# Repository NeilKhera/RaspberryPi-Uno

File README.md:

## RaspberryPi-Uno
<br/>

### Description
A pin-compatible Arduino Uno clone board for the Raspberry Pi RP2040 microcontroller.

Check out the resources folder for Circuitpython config files, or the Releases section for the compiled firmware .uf2!

### License

Designed by Neil Khera.

Creative Commons Attribution/Share-Alike, all text above must be included in any redistribution. See license.txt for additional details.

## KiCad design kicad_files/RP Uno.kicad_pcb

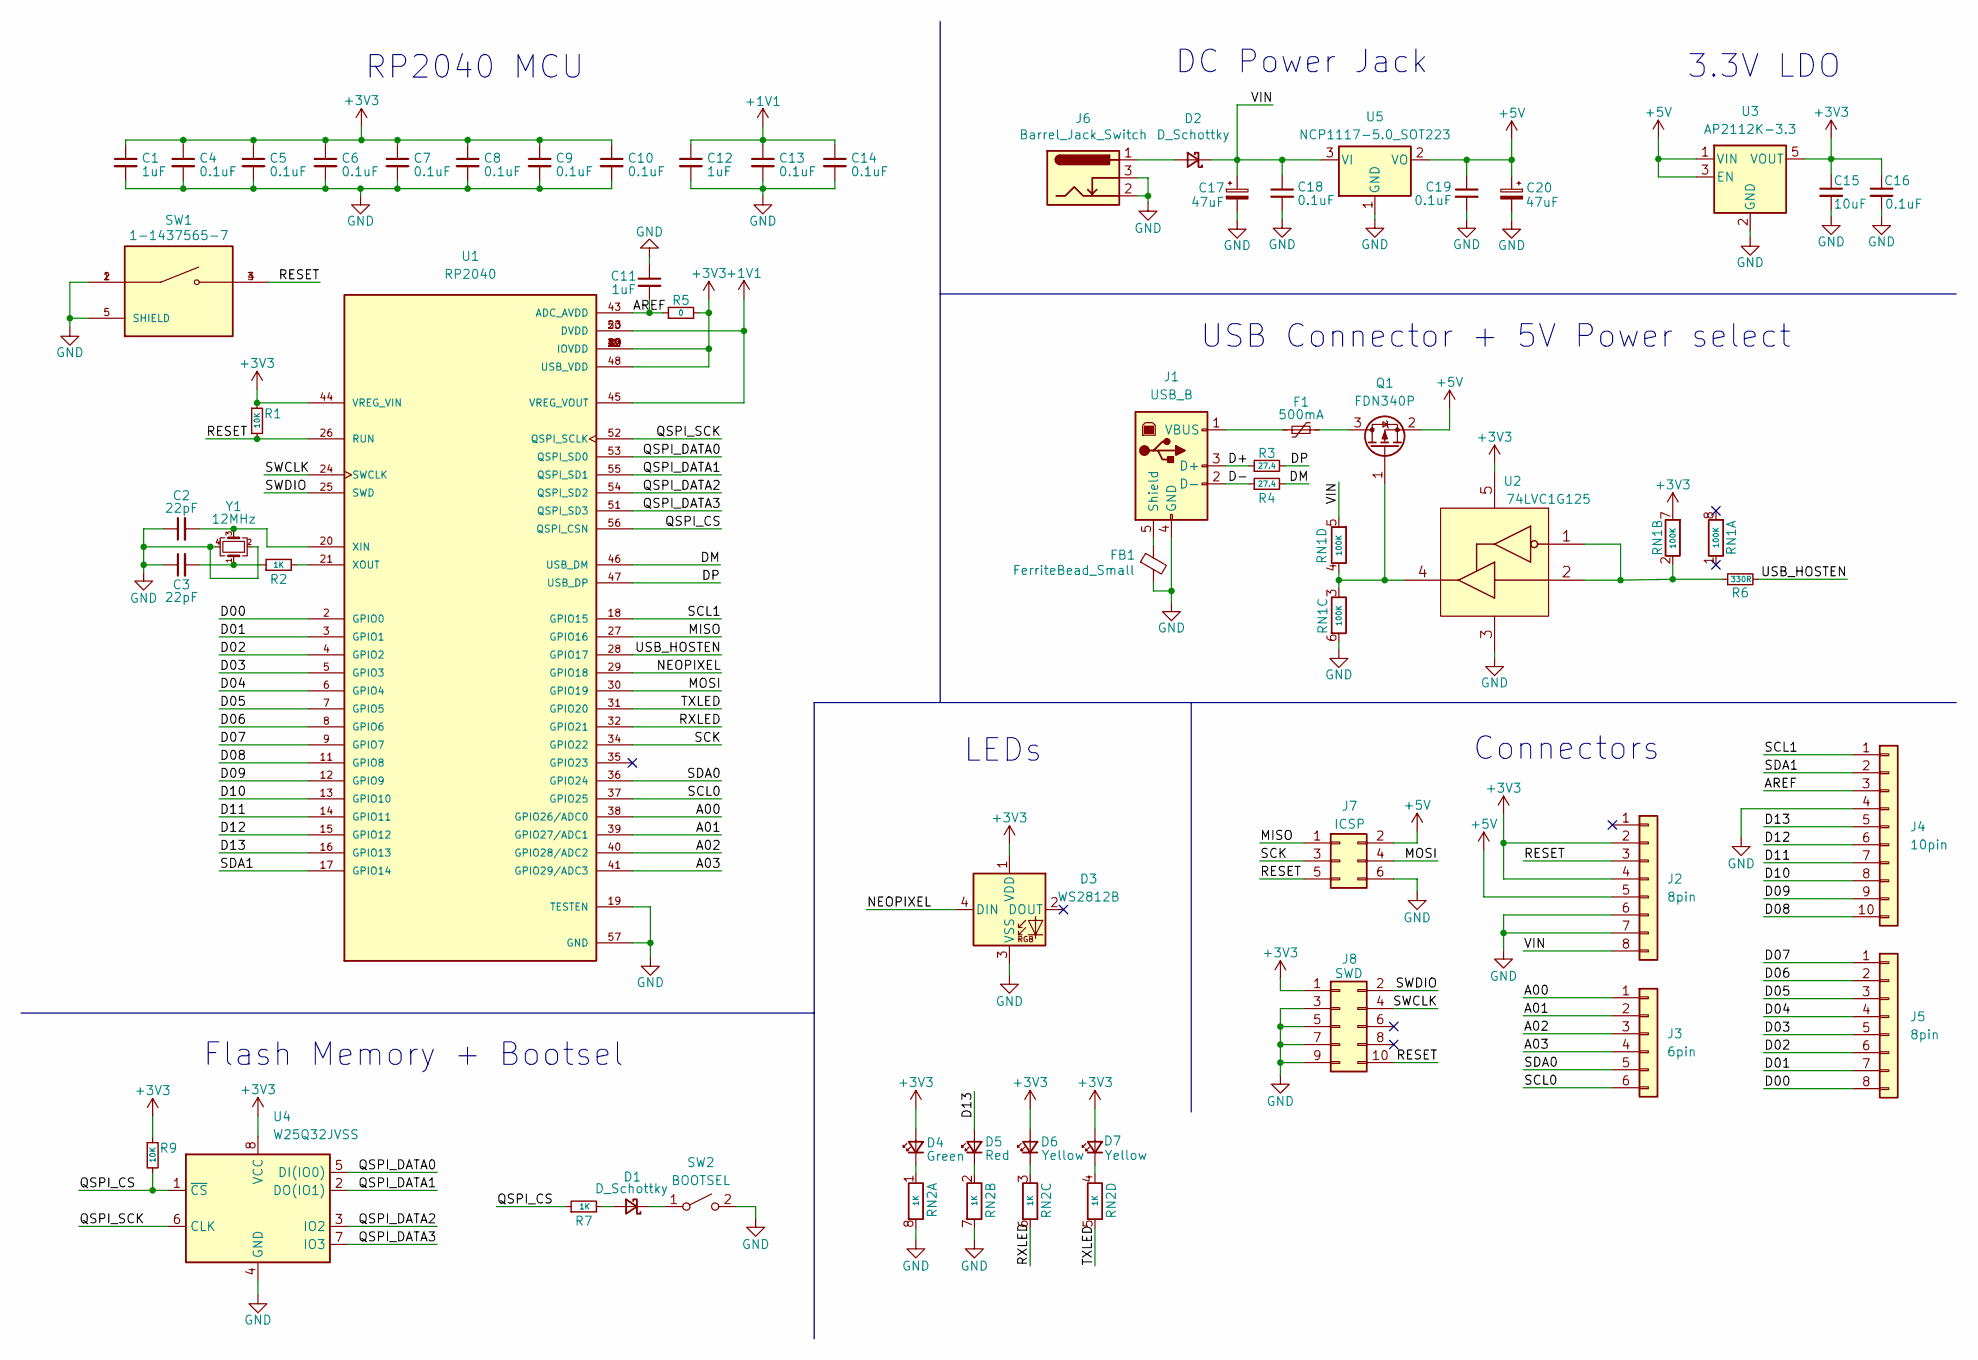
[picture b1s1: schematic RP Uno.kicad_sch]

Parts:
C1, C11, C12: 1uF; C_0603_1608Metric
C2, C3: 22pF; C_0603_1608Metric
C4, C5, C6, C7, C8, C9, C10, C13, C14, C16, C18, C19: 0.1uF; C_0603_1608Metric
C15: 10uF; C_0603_1608Metric
C17, C20: 47uF; CAPAE680X600N
D1: D_Schottky; D_SOD-323
D2: D_Schottky; D_SMB
D3: WS2812B; LED_WS2812B_PLCC4_5.0x5.0mm_P3.2mm
D4: Green; LED_0603_1608Metric
D5: Red; LED_0603_1608Metric
D6, D7: Yellow; LED_0603_1608Metric
F1: 500mA; Fuse_1206_3216Metric
FB1: FerriteBead_Small; L_0603_1608Metric
J1: USB_B; USB_B_OST_USB-B1HSxx_Horizontal
J2, J5: 8pin; PinSocket_1x08_P2.54mm_Vertical
J3: 6pin; PinSocket_1x06_P2.54mm_Vertical
J4: 10pin; PinSocket_1x10_P2.54mm_Vertical
J6: Barrel_Jack_Switch; BarrelJack_Horizontal
J7: ICSP; PinHeader_2x03_P2.54mm_Vertical
J8: SWD; 2X05_1.27MM_BOX_POSTS
Q1: FDN340P; SOT-23
R1, R9: 10K; R_0603_1608Metric
R2, R7: 1K; R_0603_1608Metric
R3, R4: 27.4; R_0603_1608Metric
R5: 0; R_0603_1608Metric
R6: 330R; R_0603_1608Metric
RN1: 100K; R_Array_Concave_4x0603
RN2: 1K; R_Array_Concave_4x0603
SW1: 1-1437565-7; SW_1-1437565-7
SW2: BOOTSEL; SW_SPST_B3U-1000P
U1: RP2040; QFN40P700X700X90-57N; PARTREV 1.6.1
U2: 74LVC1G125; SOT-23-5
U3: AP2112K-3.3; SOT-23-5
U4: W25Q32JVSS; SOIC-8_5.23x5.23mm_P1.27mm
U5: NCP1117-5.0_SOT223; SOT-223-3_TabPin2
Y1: 12MHz; Crystal_SMD_2520-4Pin_2.5x2.0mm

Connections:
+1V1: C12.1, C13.1, C14.1, U1.23 (DVDD), U1.45 (VREG_VOUT), U1.50 (DVDD)
+3V3: C1.1, C4.1, C5.1, C6.1, C7.1, C8.1, C9.1, C10.1, C15.1, C16.1, D3.1 (VDD), D4.2 (A), D6.2 (A), D7.2 (A), J2.2, J2.4, J8.1, R1.1, R5.2, R9.1, RN1.7 (R2.2), U1.1 (IOVDD), U1.10 (IOVDD), U1.22 (IOVDD), U1.33 (IOVDD), U1.42 (IOVDD), U1.44 (VREG_VIN), U1.48 (USB_VDD), U1.49 (IOVDD), U2.5 (VCC), U3.5 (VOUT), U4.8 (VCC)
+5V: C19.1, C20.1, J2.5, J7.2, Q1.2 (S), U3.1 (VIN), U3.3 (EN), U5.2 (VO)
/A00: J3.1, U1.38 (GPIO26/ADC0)
/A01: J3.2, U1.39 (GPIO27/ADC1)
/A02: J3.3, U1.40 (GPIO28/ADC2)
/A03: J3.4, U1.41 (GPIO29/ADC3)
/AREF: C11.2, J4.3, R5.1, U1.43 (ADC_AVDD)
/D00: J5.8, U1.2 (GPIO0)
/D01: J5.7, U1.3 (GPIO1)
/D02: J5.6, U1.4 (GPIO2)
/D03: J5.5, U1.5 (GPIO3)
/D04: J5.4, U1.6 (GPIO4)
/D05: J5.3, U1.7 (GPIO5)
/D06: J5.2, U1.8 (GPIO6)
/D07: J5.1, U1.9 (GPIO7)
/D08: J4.10, U1.11 (GPIO8)
/D09: J4.9, U1.12 (GPIO9)
/D10: J4.8, U1.13 (GPIO10)
/D11: J4.7, U1.14 (GPIO11)
/D12: J4.6, U1.15 (GPIO12)
/D13: D5.2 (A), J4.5, U1.16 (GPIO13)
/D+: J1.3 (D+), R3.1
/D-: J1.2 (D-), R4.1
/DM: R4.2, U1.46 (USB_DM)
/DP: R3.2, U1.47 (USB_DP)
/MISO: J7.1, U1.27 (GPIO16)
/MOSI: J7.4, U1.30 (GPIO19)
/NEOPIXEL: D3.4 (DIN), U1.29 (GPIO18)
/QSPI_CS: R7.1, R9.2, U1.56 (QSPI_CSN), U4.1 (~CS)
/QSPI_DATA0: U1.53 (QSPI_SD0), U4.5 (DI(IO0))
/QSPI_DATA1: U1.55 (QSPI_SD1), U4.2 (DO(IO1))
/QSPI_DATA2: U1.54 (QSPI_SD2), U4.3 (IO2)
/QSPI_DATA3: U1.51 (QSPI_SD3), U4.7 (IO3)
/QSPI_SCK: U1.52 (QSPI_SCLK), U4.6 (CLK)
/RESET: J2.3, J7.5, J8.10, R1.2, SW1.3, SW1.4, U1.26 (RUN)
/RXLED: RN2.6 (R3.2), U1.32 (GPIO21)
/SCK: J7.3, U1.34 (GPIO22)
/SCL0: J3.6, U1.37 (GPIO25)
/SCL1: J4.1, U1.18 (GPIO15)
/SDA0: J3.5, U1.36 (GPIO24)
/SDA1: J4.2, U1.17 (GPIO14)
/SWCLK: J8.4, U1.24 (SWCLK)
/SWDIO: J8.2, U1.25 (SWD)
/TXLED: RN2.5 (R4.2), U1.31 (GPIO20)
/USB_HOSTEN: R6.2, U1.28 (GPIO17)
/VIN: C17.1, C18.1, D2.1 (K), J2.8, RN1.5 (R4.2), U5.3 (VI); also elsewhere on the board
GND: C1.2, C2.1, C3.1, C4.2, C5.2, C6.2, C7.2, C8.2, C9.2, C10.2, C11.1, C12.2, C13.2, C14.2, C15.2, C16.2, C17.2, C18.2, C19.2, C20.2, D3.3 (VSS), FB1.2, J1.4 (GND), J2.6, J2.7, J4.4, J6.2, J6.3, J7.6, J8.3, J8.5, J8.7, J8.9, RN1.6 (R3.2), RN2.7 (R2.2), RN2.8 (R1.2), SW1.1, SW1.2, SW1.5 (SHIELD), SW2.2 (B), U1.19 (TESTEN), U1.57 (GND), U2.3 (GND), U3.2 (GND), U4.4 (GND), U5.1 (GND), Y1.2, Y1.4; also elsewhere on the board
unnamed: C2.2, U1.20 (XIN), Y1.3
unnamed: C3.2, R2.1, Y1.1
unnamed: D2.2 (A), J6.1
unnamed: D4.1 (K), RN2.1 (R1.1)
unnamed: D5.1 (K), RN2.2 (R2.1)
unnamed: D6.1 (K), RN2.3 (R3.1)
unnamed: D7.1 (K), RN2.4 (R4.1)
unnamed: F1.1, J1.1 (VBUS)
unnamed: F1.2, Q1.3 (D)
unnamed: FB1.1, J1.5 (Shield)
unnamed: Q1.1 (G), RN1.3 (R3.1), RN1.4 (R4.1), U2.4 (Y)
unnamed: R2.2, U1.21 (XOUT)
unnamed: R6.1, RN1.2 (R2.1), U2.1 (OE_N), U2.2 (A)
unnamed: D1.2 (A), R7.2
unnamed: D1.1 (K), SW2.1 (A)

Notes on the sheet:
Flash Memory + Bootsel
3.3V LDO
LEDs
USB Connector + 5V Power select
Connectors
RP2040 MCU
DC Power Jack

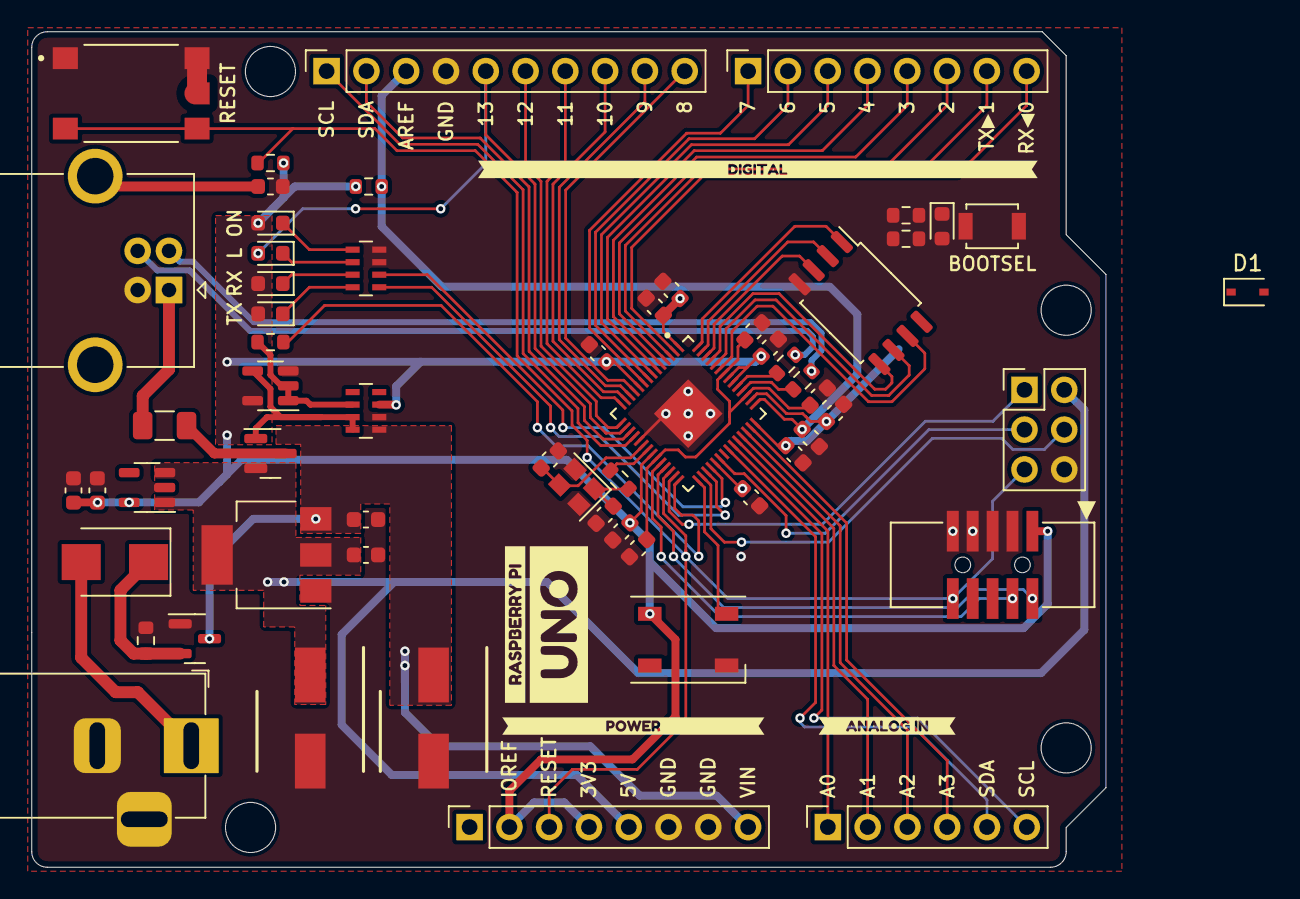
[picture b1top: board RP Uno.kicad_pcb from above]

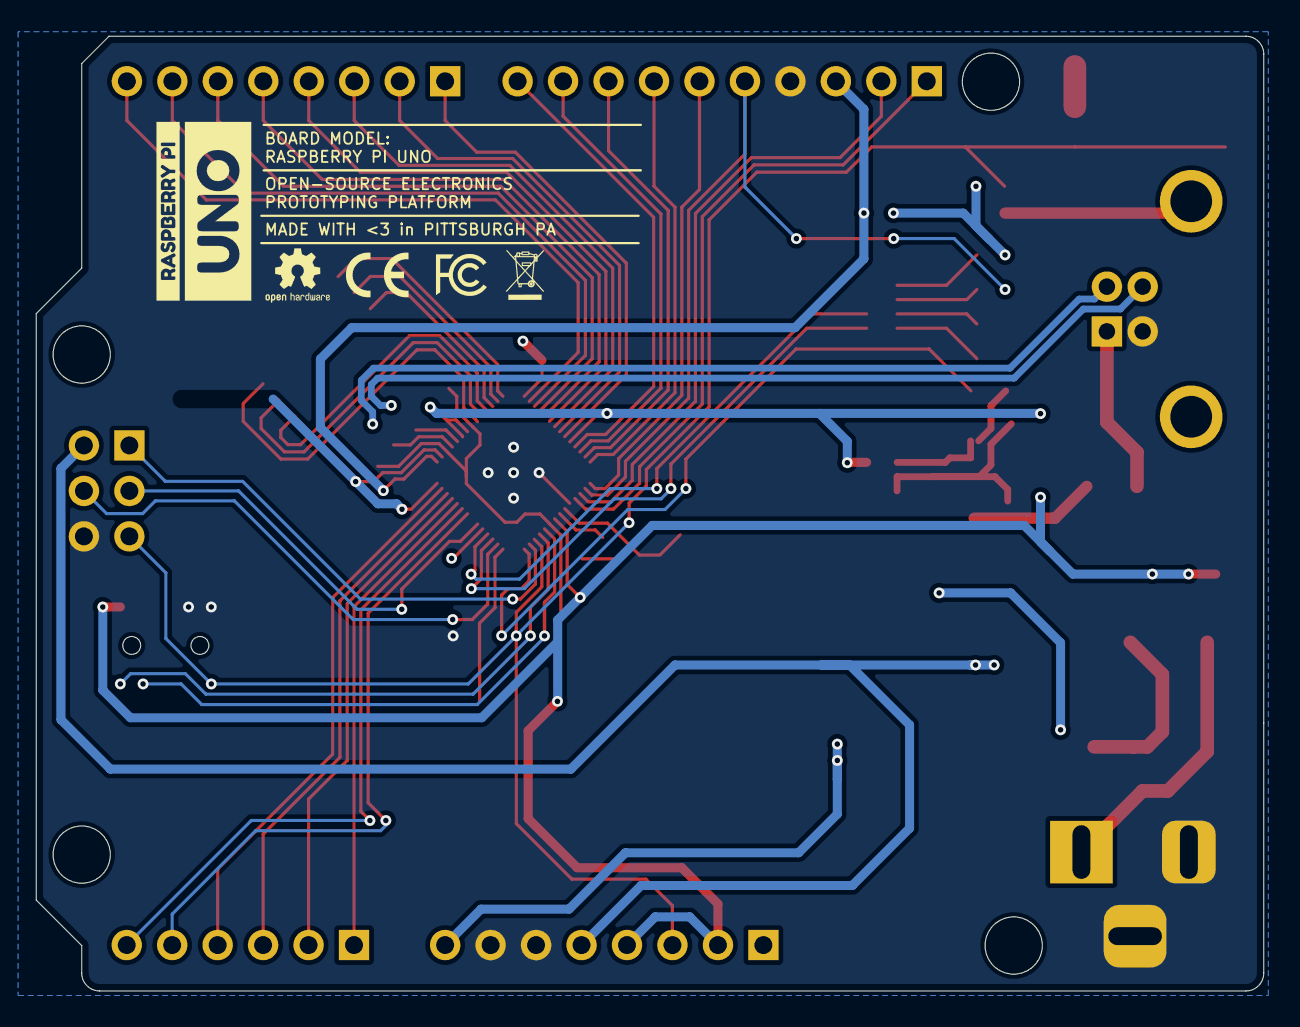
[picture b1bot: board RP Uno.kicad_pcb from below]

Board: 2 copper layers, 68.6 x 53.3 mm, 70 parts (2 on the bottom side), 64 nets.

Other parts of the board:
@HOLE0, @HOLE1, @HOLE2, @HOLE3: (no value)
D1#2: Blue; LED_0603_1608Metric
Q2: FDN340P; SOT-23
R8: 10K; R_0603_1608Metric
kibuzzard-639FD1FE: G***; kibuzzard-639FD1FE
kibuzzard-639FD3EE: G***; kibuzzard-639FD3EE
kibuzzard-639FD17E, kibuzzard-639FD17E#2: G***; kibuzzard-639FD17E
kibuzzard-639FD42A: G***; kibuzzard-639FD42A
kibuzzard-639FD142, kibuzzard-639FD142#2: G***; kibuzzard-639FD142

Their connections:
/VIN: Q2.3 (D); also elsewhere on the board
GND: Q2.1 (G), R8.2; also elsewhere on the board
unnamed: Q2.2 (S), R8.1

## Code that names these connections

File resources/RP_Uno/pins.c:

#include "shared-bindings/board/__init__.h"

STATIC const mp_rom_map_elem_t board_module_globals_table[] = {
    CIRCUITPYTHON_BOARD_DICT_STANDARD_ITEMS

    { MP_ROM_QSTR(MP_QSTR_TX0), MP_ROM_PTR(&pin_GPIO0) },
    { MP_ROM_QSTR(MP_QSTR_RX0), MP_ROM_PTR(&pin_GPIO1) },

    { MP_ROM_QSTR(MP_QSTR_D0), MP_ROM_PTR(&pin_GPIO0) },
    { MP_ROM_QSTR(MP_QSTR_D1), MP_ROM_PTR(&pin_GPIO1) },
    { MP_ROM_QSTR(MP_QSTR_D2), MP_ROM_PTR(&pin_GPIO2) },
    { MP_ROM_QSTR(MP_QSTR_D3), MP_ROM_PTR(&pin_GPIO3) },
    { MP_ROM_QSTR(MP_QSTR_D4), MP_ROM_PTR(&pin_GPIO4) },
    { MP_ROM_QSTR(MP_QSTR_D5), MP_ROM_PTR(&pin_GPIO5) },
    { MP_ROM_QSTR(MP_QSTR_D6), MP_ROM_PTR(&pin_GPIO6) },
    { MP_ROM_QSTR(MP_QSTR_D7), MP_ROM_PTR(&pin_GPIO7) },
    { MP_ROM_QSTR(MP_QSTR_D8), MP_ROM_PTR(&pin_GPIO8) },
    { MP_ROM_QSTR(MP_QSTR_D9), MP_ROM_PTR(&pin_GPIO9) },
    { MP_ROM_QSTR(MP_QSTR_D10), MP_ROM_PTR(&pin_GPIO10) },
    { MP_ROM_QSTR(MP_QSTR_D11), MP_ROM_PTR(&pin_GPIO11) },
    { MP_ROM_QSTR(MP_QSTR_D12), MP_ROM_PTR(&pin_GPIO12) },
    { MP_ROM_QSTR(MP_QSTR_D13), MP_ROM_PTR(&pin_GPIO13) },

    { MP_ROM_QSTR(MP_QSTR_LED), MP_ROM_PTR(&pin_GPIO13) },


    { MP_ROM_QSTR(MP_QSTR_SDA1), MP_ROM_PTR(&pin_GPIO14) },
    { MP_ROM_QSTR(MP_QSTR_SCL1), MP_ROM_PTR(&pin_GPIO15) },

    { MP_ROM_QSTR(MP_QSTR_MISO), MP_ROM_PTR(&pin_GPIO16) },
    { MP_ROM_QSTR(MP_QSTR_MOSI), MP_ROM_PTR(&pin_GPIO19) },
    { MP_ROM_QSTR(MP_QSTR_SCK), MP_ROM_PTR(&pin_GPIO22) },

    { MP_ROM_QSTR(MP_QSTR_NEOPIXEL), MP_ROM_PTR(&pin_GPIO18) },
    { MP_ROM_QSTR(MP_QSTR_LED_TX), MP_ROM_PTR(&pin_GPIO20) },
    { MP_ROM_QSTR(MP_QSTR_LED_RX), MP_ROM_PTR(&pin_GPIO21) },

    { MP_ROM_QSTR(MP_QSTR_SDA0), MP_ROM_PTR(&pin_GPIO24) },
    { MP_ROM_QSTR(MP_QSTR_SCL0), MP_ROM_PTR(&pin_GPIO25) },


    { MP_ROM_QSTR(MP_QSTR_A0), MP_ROM_PTR(&pin_GPIO26) },
    { MP_ROM_QSTR(MP_QSTR_A1), MP_ROM_PTR(&pin_GPIO27) },
    { MP_ROM_QSTR(MP_QSTR_A2), MP_ROM_PTR(&pin_GPIO28) },
    { MP_ROM_QSTR(MP_QSTR_A3), MP_ROM_PTR(&pin_GPIO29) },


    { MP_ROM_QSTR(MP_QSTR_I2C), MP_ROM_PTR(&board_i2c_obj) },
    { MP_ROM_QSTR(MP_QSTR_SPI), MP_ROM_PTR(&board_spi_obj) },
    { MP_ROM_QSTR(MP_QSTR_UART), MP_ROM_PTR(&board_uart_obj) },
};
MP_DEFINE_CONST_DICT(board_module_globals, board_module_globals_table);

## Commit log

2022-12-19 Pinout changes and silkscreen additions
2023-01-24 Moved stuff around, and added circuitpython firmware config files
2023-06-20 Partial Rev 2 updates
